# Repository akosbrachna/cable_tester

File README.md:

# cable_tester

Simple cable tester for checking CAT network cables. It can check wiring issues as well as cable length.

Wiring mismatch testing is based on voltage division.

Cable length measurement is based on signal reflection.

The microcontroller is a PIC18F45k50. This model is used because it has a CTMU unit that enables the 
microcontroller to measure nanosecond short times which is required for cable length measurement. 
The C program was written in MPLAB IDE.

The SMD circuit was designed in Eagle CAD circuit designer. The PCB is double-layered.
Future plan is to add another comparator and make cable length measurement on all 4 pairs.

Master circuit schematic:

Remote circuit schematic:

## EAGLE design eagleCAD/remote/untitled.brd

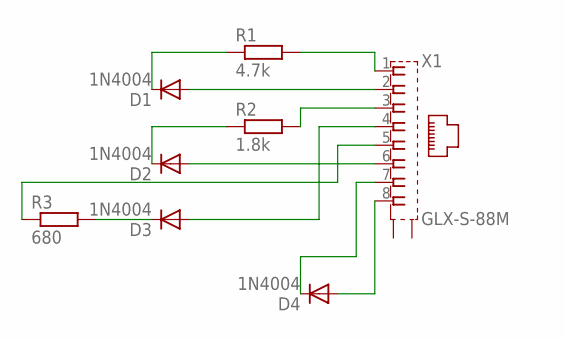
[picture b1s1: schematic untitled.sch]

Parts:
D1, D2, D3, D4: 1N4004; DO41-10; MPN 1N4004-E3/54
R1: 4.7k; 0309/12; MPN MCMF0W4FF4701A50
R2: 1.8k; 0309/12; MPN MCMF0W4FF1801A50
R3: 680; 0309/12; MPN MF50 680R
X1: GLX-S-88M

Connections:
unnamed: D1.A, X1.2
unnamed: D1.C, R1.1
unnamed: R1.2, X1.1
unnamed: D2.A, X1.6
unnamed: D2.C, R2.1
unnamed: R2.2, X1.3
unnamed: D3.A, X1.4
unnamed: D3.C, R3.2
unnamed: R3.1, X1.5
unnamed: D4.A, X1.8
unnamed: D4.C, X1.7

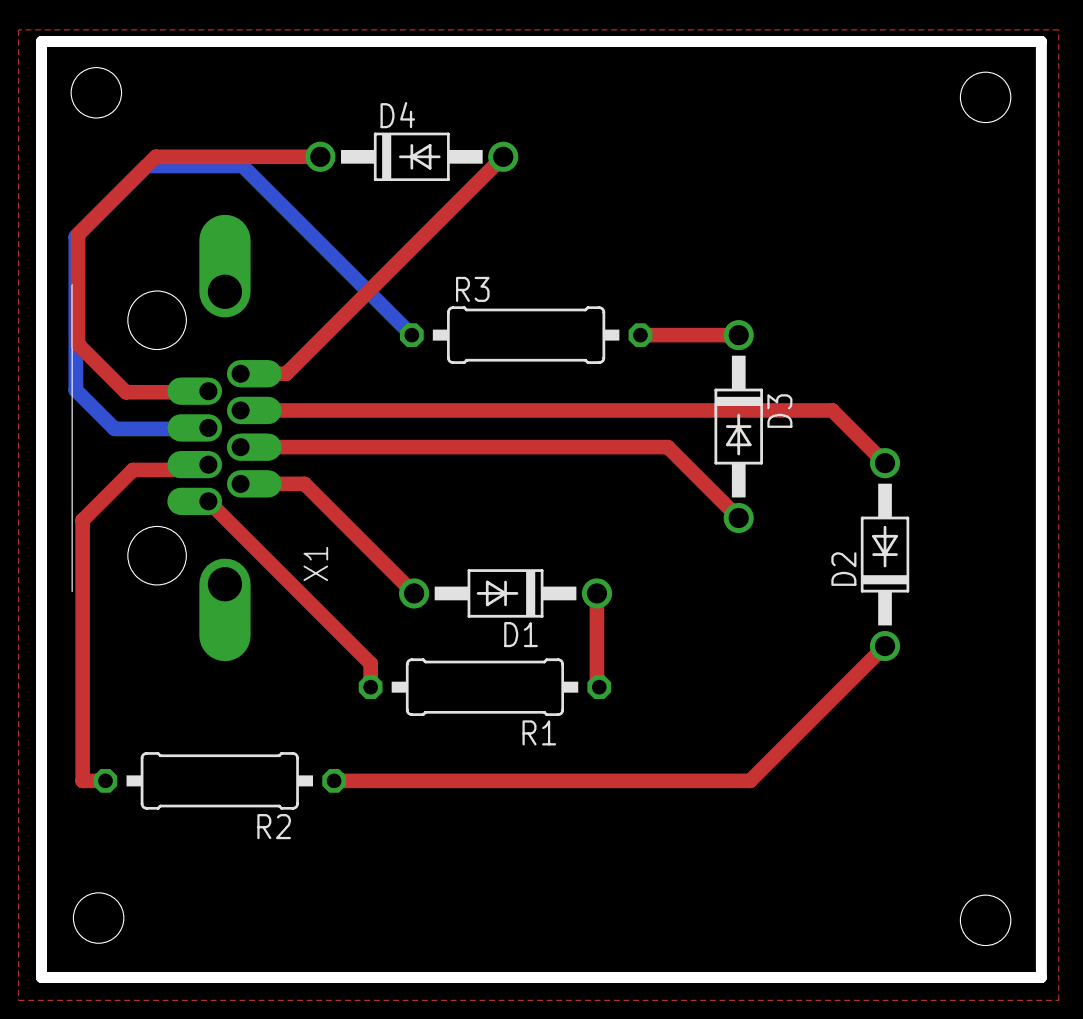
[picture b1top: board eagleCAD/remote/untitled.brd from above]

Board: 2 copper layers, 55.5 x 52.0 mm, 8 parts (0 on the bottom side), 11 nets.

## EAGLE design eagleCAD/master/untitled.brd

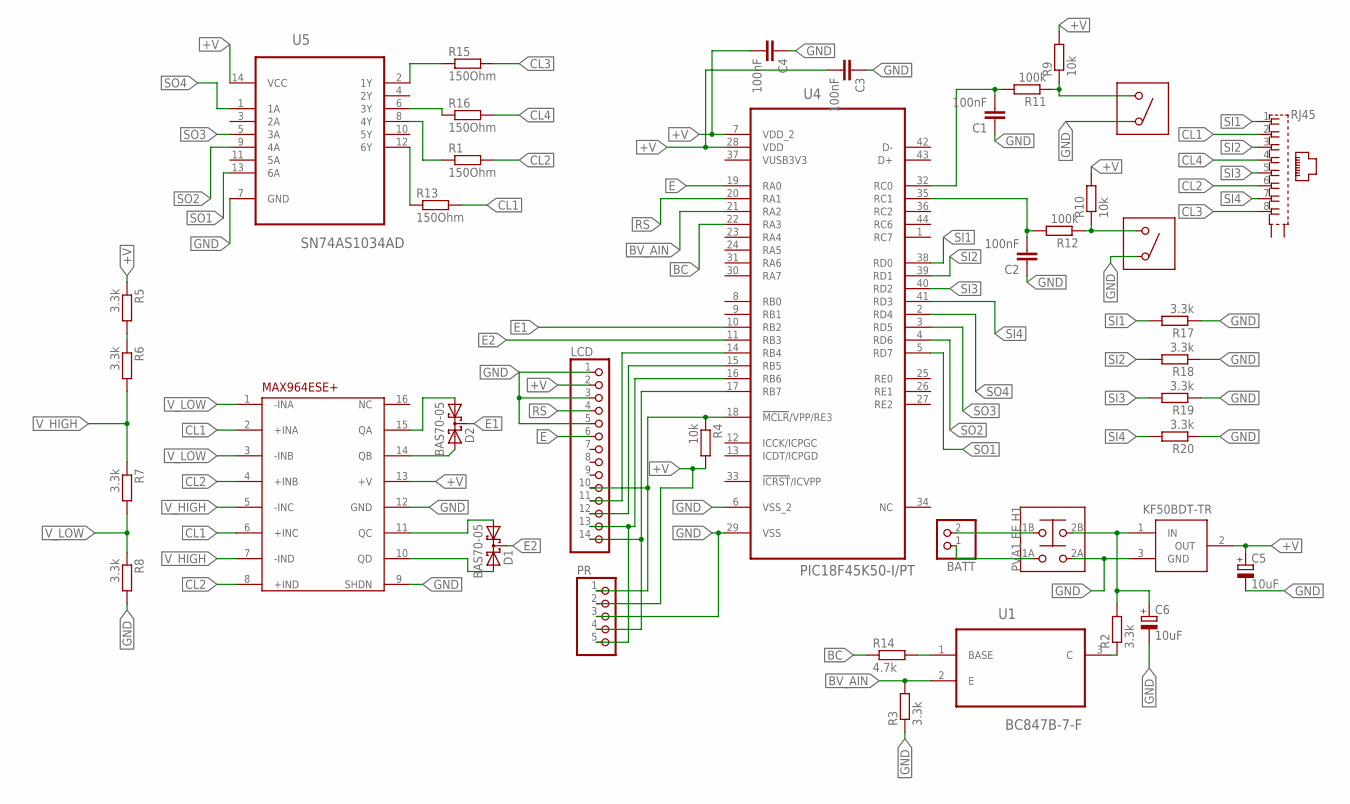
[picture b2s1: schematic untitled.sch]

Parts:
BATT: PINHD-1X2; 1X02
C1, C2, C3, C4: 100nF; C0603; MPN CC0603KRX7R7BB104
C5, C6: 10uF; 153CLV-0405; MPN 16TZV10M4X6.1
D1, D2: BAS70-05; SOT23
LCD: PINHD-1X14; 1X14
PR: PINHD-1X5; 1X05
R1, R13, R15, R16: 150Ohm; R0603; MPN CPF0603F150RC1
R2, R3, R5, R6, R7, R8, R17, R18, R19, R20: 3.3k; R0603; MPN CRGH0603F3K3
R4, R9, R10: 10k; R0603; MPN CRCW060310K0FKTA
R11, R12: 100k; R0603; MPN CRGH0603J100K
R14: 4.7k; R0603; MPN CRCW06034K70FKEA
RJ45: 1-406541-6; RJ45
U1: BC847B-7-F; SOT95P240X110-3N
U4: PIC18F45K50-I/PT; TQFP80P1200X1200X120-44N
U5: SN74AS1034AD; SOIC127P600X175-14N
U$1: KF50BDT-TR; TO252
U$2: MAX964ESE+; SO16; MPN MAX964ESE+
U$3: PVA1_EE_H1
U$4, U$5: FSM4JRT; MPN FSM4JRT

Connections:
+V: C3.2, C4.2, C5.+, LCD.2, PR.2, R4.2, R5.1, R9.2, R10.2, U4.7 (VDD_2), U4.28 (VDD), U5.14 (VCC), U$1.2 (OUT), U$2.13 (+V)
BC: R14.1, U4.22 (RA3)
BV_AIN: R3.2, U1.2 (E), U4.21 (RA2)
CL1: R13.2, RJ45.2, U$2.2 (+INA), U$2.6 (+INC)
CL2: R1.2, RJ45.6, U$2.4 (+INB), U$2.8 (+IND)
CL3: R15.2, RJ45.8
CL4: R16.2, RJ45.4
E: LCD.6, U4.19 (RA0)
E1: D2.3 (C), U4.10 (RB2)
E2: D1.3 (C), U4.11 (RB3)
GND: C1.1, C2.1, C3.1, C4.1, C5.-, C6.-, LCD.1, LCD.3, LCD.5, PR.3, R3.1, R8.2, R17.1, R18.1, R19.1, R20.1, U4.6 (VSS_2), U4.29 (VSS), U5.7 (GND), U$1.3 (GND), U$2.9 (SHDN), U$2.12 (GND), U$3.2A, U$4.2, U$5.2
MCLR: LCD.10, PR.1, R4.1, U4.18 (!MCLR!/VPP/RE3)
unnamed: LCD.11, U4.14 (RB4)
unnamed: LCD.12, U4.15 (RB5)
unnamed: R14.2, U1.1 (BASE)
unnamed: R2.1, U1.3 (C)
unnamed: R1.1, U5.8 (4Y)
unnamed: R13.1, U5.12 (6Y)
unnamed: R16.1, U5.6 (3Y)
unnamed: LCD.13, PR.5, U4.16 (RB6)
unnamed: C1.2, R11.2, U4.32 (RC0)
unnamed: BATT.2, U$3.1B
unnamed: R15.1, U5.2 (1Y)
unnamed: BATT.1, U$3.1A
unnamed: LCD.14, PR.4, U4.17 (RB7)
unnamed: D2.1 (A1), U$2.15 (QA)
unnamed: R5.2, R6.1
unnamed: D2.2 (A2), U$2.14 (QB)
unnamed: D1.1 (A1), U$2.11 (QC)
unnamed: R9.1, R11.1, U$4.1
unnamed: D1.2 (A2), U$2.10 (QD)
unnamed: C2.2, R12.2, U4.35 (RC1)
unnamed: R10.1, R12.1, U$5.1
unnamed: C6.+, R2.2, U$1.1 (IN), U$3.2B
RS: LCD.4, U4.20 (RA1)
SI1: R17.2, RJ45.1, U4.38 (RD0)
SI2: R18.2, RJ45.3, U4.39 (RD1)
SI3: R19.2, RJ45.5, U4.40 (RD2)
SI4: R20.2, RJ45.7, U4.41 (RD3)
SO1: U4.5 (RD7), U5.13 (6A)
SO2: U4.4 (RD6), U5.9 (4A)
SO3: U4.3 (RD5), U5.5 (3A)
SO4: U4.2 (RD4), U5.1 (1A)
VUSB3V3: U4.37 (VUSB3V3)
V_HIGH: R6.2, R7.1, U$2.5 (-INC), U$2.7 (-IND)
V_LOW: R7.2, R8.1, U$2.1 (-INA), U$2.3 (-INB)

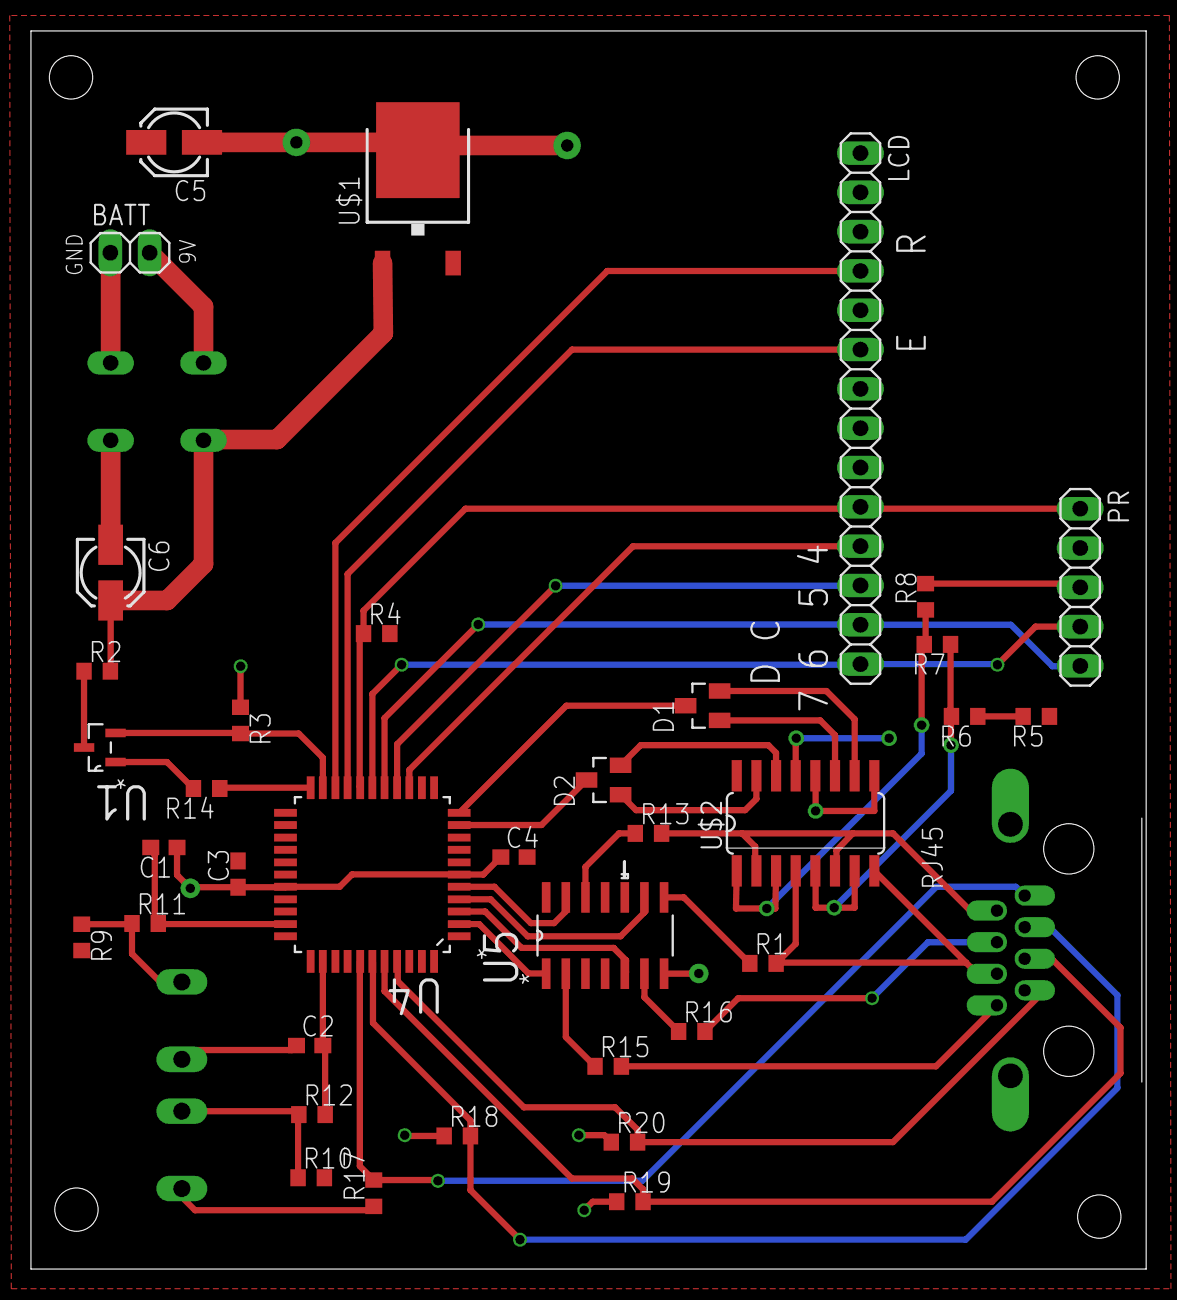
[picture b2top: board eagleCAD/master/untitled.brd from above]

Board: 2 copper layers, 72.1 x 80.0 mm, 40 parts (0 on the bottom side), 45 nets.

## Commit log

2017-06-26 removed unnecessary headers from main.c
2017-06-27 added remote circuit schematic and eagle CAD files
2017-06-27 edited readme
2017-06-27 edited picture
2017-07-07 added picture
